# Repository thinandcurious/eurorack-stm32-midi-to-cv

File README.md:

# MIDI to CV

## STLink Pins

- VDD (Do not connect)
- SWCLK
- GND
- SWDIO
- RST
- SWO

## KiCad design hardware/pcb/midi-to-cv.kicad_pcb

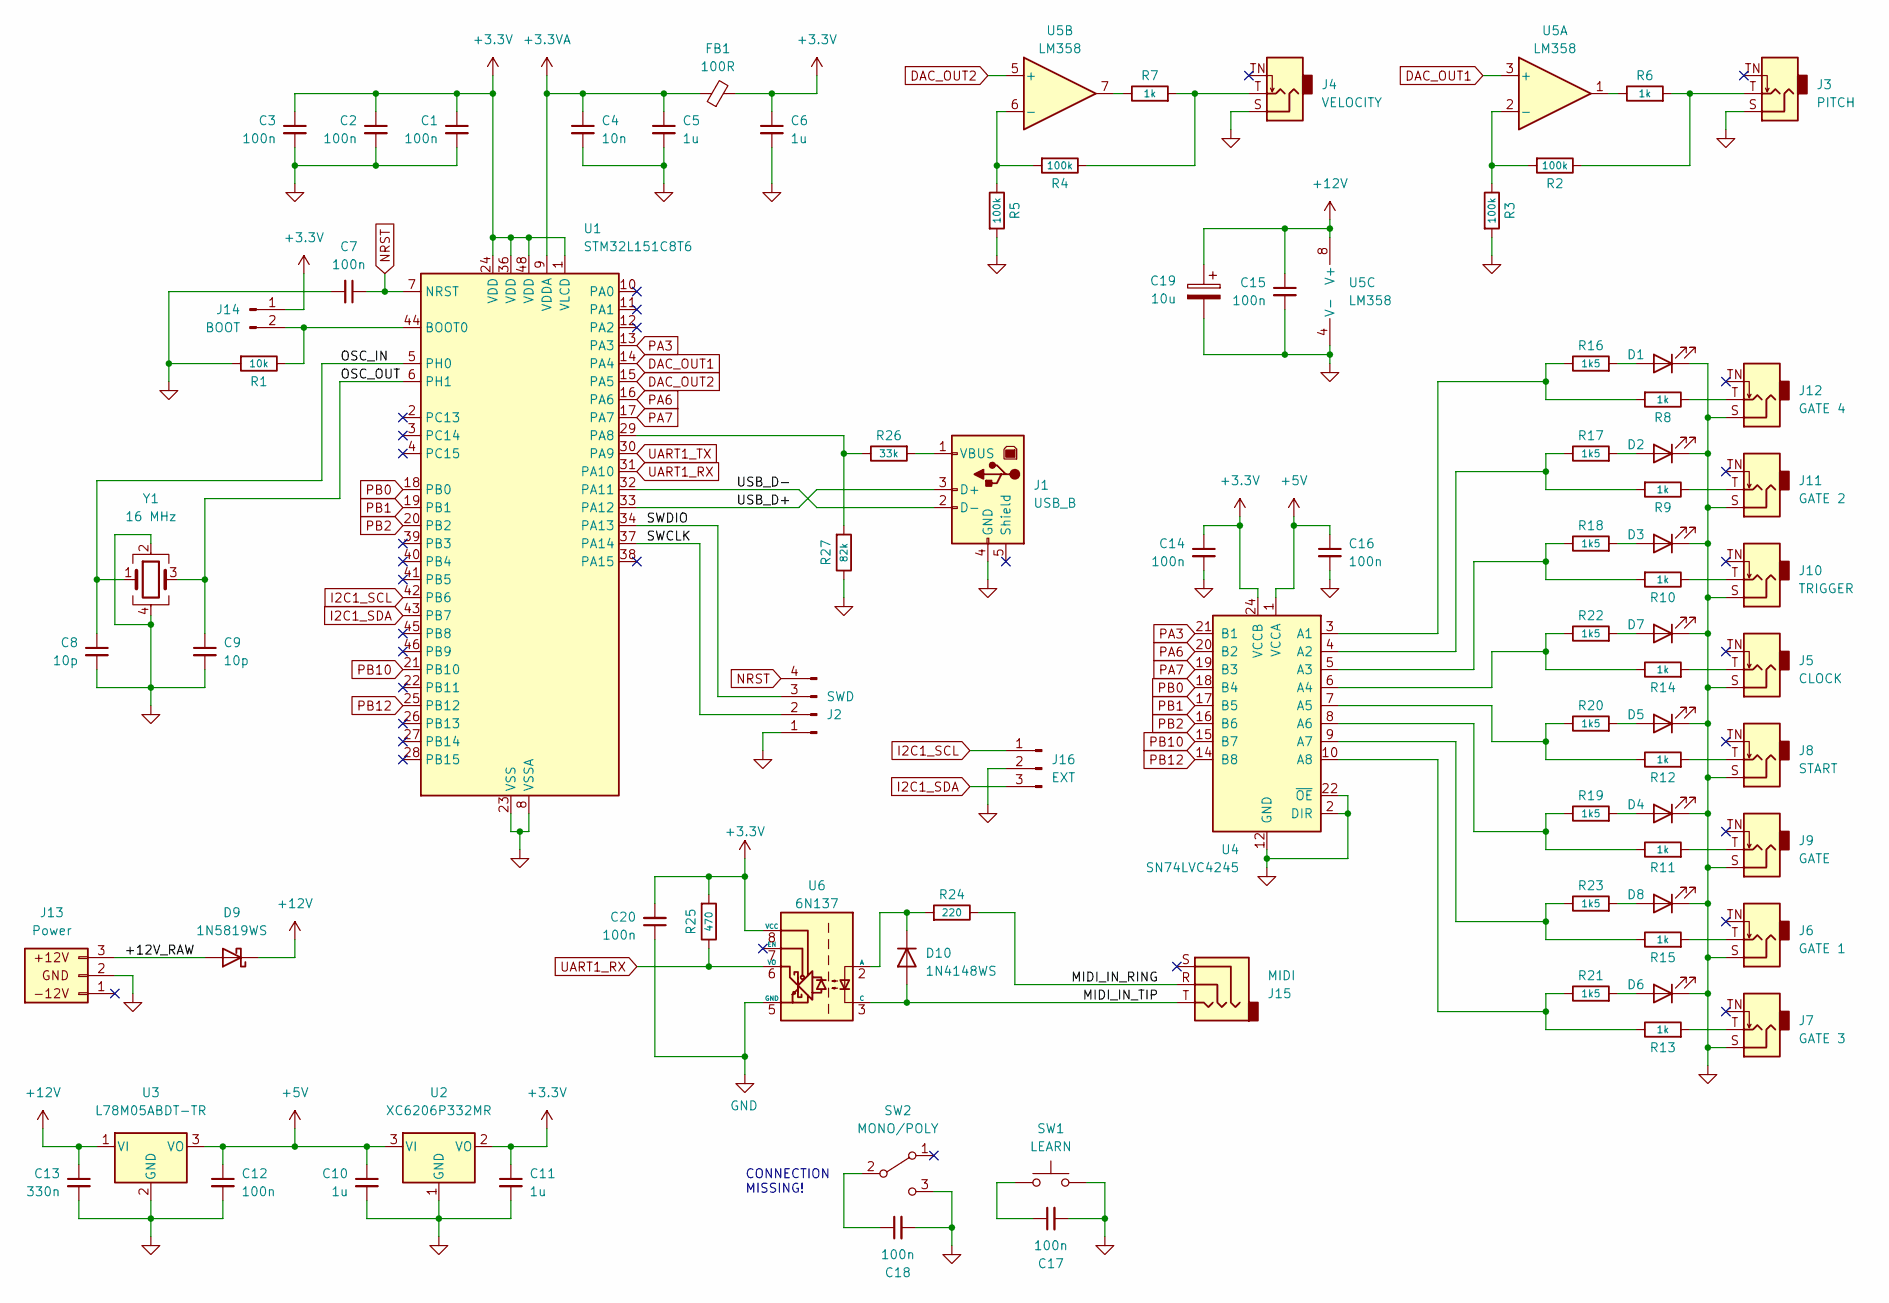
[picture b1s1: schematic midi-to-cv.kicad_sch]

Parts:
C1, C2, C3, C7, C14, C15, C16, C17, C18: 100n; C_0402_1005Metric; LCSC C307331
C4: 10n; C_0402_1005Metric; LCSC C15195
C5, C6, C10, C11: 1u; C_0805_2012Metric; LCSC C28323
C8, C9: 10p; C_0402_1005Metric; LCSC C32949
C12: 100n; C_0805_2012Metric; LCSC C49678
C13: 330n; C_0805_2012Metric; LCSC C1740
C19: 10u; C_1206_3216Metric; LCSC C13585
C20: 100n; C_0603_1608Metric; LCSC C14663
D1, D2, D3, D4, D5, D6, D7, D8: LED; LED_D3.0mm_Centered
D9: 1N5819WS; D_SOD-323; LCSC C191023
D10: 1N4148WS; D_SOD-323; LCSC 1N4148WS
FB1: 100R; L_0805_2012Metric; LCSC C1002
J1: USB_B; Reichelt_FIS-USB-2-B-180
J2: SWD; PinHeader_1x04_P2.54mm_Vertical
J3: PITCH; Jack_3.5mm_PJ398SM_Vertical
J4: VELOCITY; Jack_3.5mm_PJ398SM_Vertical
J5: CLOCK; Jack_3.5mm_PJ398SM_Vertical
J6: GATE 1; Jack_3.5mm_PJ398SM_Vertical
J7: GATE 3; Jack_3.5mm_PJ398SM_Vertical
J8: START; Jack_3.5mm_PJ398SM_Vertical
J9: GATE; Jack_3.5mm_PJ398SM_Vertical
J10: TRIGGER; Jack_3.5mm_PJ398SM_Vertical
J11: GATE 2; Jack_3.5mm_PJ398SM_Vertical
J12: GATE 4; Jack_3.5mm_PJ398SM_Vertical
J13: Power; JST_XH_B3B-XH-A_1x03_P2.50mm_Vertical
J14: BOOT; PinHeader_1x02_P2.54mm_Vertical
J15: MIDI; Jack_3.5mm_PJ366ST_Vertical
J16: EXT; PinHeader_1x03_P2.54mm_Vertical
R1: 10k; R_0603_1608Metric; LCSC C25804
R2, R3, R4, R5: 100k; R_0603_1608Metric; LCSC C25803
R6, R7, R8, R9, R10, R11, R12, R13, R14, R15: 1k; R_0603_1608Metric; LCSC C21190
R16, R17, R18, R19, R20, R21, R22, R23: 1k5; R_0603_1608Metric; LCSC C22843
R24: 220; R_0603_1608Metric; LCSC C22962
R25: 470; R_0603_1608Metric; LCSC C23179
R26: 33k; R_0603_1608Metric; LCSC C4216
R27: 82k; R_0603_1608Metric; LCSC C23254
SW1: LEARN; Switch_Push_6mm
SW2: MONO/POLY; Switch_SPDT_Micro-Toggle
U1: STM32L151C8T6; LQFP-48_7x7mm_P0.5mm; LCSC C9861
U2: XC6206P332MR; SOT-23-3; LCSC C5446
U3: L78M05ABDT-TR; TO-252-2; LCSC C58069
U4: SN74LVC4245; TSSOP-24_4.4x7.8mm_P0.65mm; LCSC C7859
U5: LM358; SOIC-8_3.9x4.9mm_P1.27mm; LCSC C7950
U6: 6N137; SSO-8_6.7x9.8mm_P2.54mm_Clearance8mm; LCSC C110020
Y1: 16 MHz; Crystal_SMD_3225-4Pin_3.2x2.5mm; LCSC C13738

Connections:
+3.3V: C1.1, C2.1, C3.1, C6.1, C11.1, C14.1, C20.2, FB1.2, J14.1, R25.2, U1.1 (VLCD), U1.24 (VDD), U1.36 (VDD), U1.48 (VDD), U2.2 (VO), U4.23 (VCCB), U4.24 (VCCB), U6.8 (VCC)
+3.3VA: C4.1, C5.1, FB1.1, U1.9 (VDDA)
+5V: C10.1, C12.1, C16.1, U2.3 (VI), U3.3 (VO), U4.1 (VCCA)
+12V: C13.1, C15.1, C19.1, D9.1 (K), U3.1 (VI), U5.8 (V+)
/+12V_RAW: D9.2 (A), J13.3
/MIDI_IN_RING: J15.R, R24.1
/MIDI_IN_TIP: D10.2 (A), J15.T, U6.3 (C)
/OSC_IN: C8.1, U1.5 (PH0), Y1.1
/OSC_OUT: C9.1, U1.6 (PH1), Y1.3
/SWCLK: J2.2, U1.37 (PA14)
/SWDIO: J2.3, U1.34 (PA13)
/USB_D+: J1.3 (D+), U1.33 (PA12)
/USB_D-: J1.2 (D-), U1.32 (PA11)
DAC_OUT1: U1.14 (PA4), U5.3 (+)
DAC_OUT2: U1.15 (PA5), U5.5 (+)
GND: C1.2, C2.2, C3.2, C4.2, C5.2, C6.2, C7.2, C8.2, C9.2, C10.2, C11.2, C12.2, C13.2, C14.2, C15.2, C16.2, C17.2, C18.2, C19.2, C20.1, D1.1 (K), D2.1 (K), D3.1 (K), D4.1 (K), D5.1 (K), D6.1 (K), D7.1 (K), D8.1 (K), J1.4 (GND), J2.1, J3.S, J4.S, J5.S, J6.S, J7.S, J8.S, J9.S, J10.S, J11.S, J12.S, J13.2, J16.2, R1.2, R3.2, R5.2, R27.1, SW1.2, SW2.3 (C), U1.8 (VSSA), U1.23 (VSS), U1.35 (VSS), U1.47 (VSS), U2.1 (GND), U3.2 (GND), U4.2 (DIR), U4.11 (GND), U4.12 (GND), U4.13 (GND), U4.22 (~OE), U5.4 (V-), U6.5 (GND), Y1.2, Y1.4
I2C1_SCL: J16.1, U1.42 (PB6)
I2C1_SDA: J16.3, U1.43 (PB7)
NRST: C7.1, J2.4, U1.7 (NRST)
unnamed: C17.1, SW1.1
unnamed: D1.2 (A), R16.2
unnamed: D2.2 (A), R17.2
unnamed: D3.2 (A), R18.2
unnamed: D4.2 (A), R19.2
unnamed: D5.2 (A), R20.2
unnamed: D6.2 (A), R21.2
unnamed: D7.2 (A), R22.2
unnamed: D8.2 (A), R23.2
unnamed: D10.1 (K), R24.2, U6.2 (A)
unnamed: J1.1 (VBUS), R26.2
unnamed: J3.T, R2.1, R6.2
unnamed: J4.T, R4.1, R7.2
unnamed: J5.T, R14.2
unnamed: J6.T, R15.2
unnamed: J7.T, R13.2
unnamed: J8.T, R12.2
unnamed: J9.T, R11.2
unnamed: J10.T, R10.1
unnamed: J11.T, R9.1
unnamed: J12.T, R8.1
unnamed: J14.2, R1.1, U1.44 (BOOT0)
unnamed: R6.1, U5.1
unnamed: R7.1, U5.7
unnamed: C18.1, SW2.2 (B)
unnamed: R26.1, R27.2, U1.29 (PA8)
unnamed: R8.2, R16.1, U4.3 (A1)
unnamed: R9.2, R17.1, U4.4 (A2)
unnamed: R10.2, R18.1, U4.5 (A3)
unnamed: R14.1, R22.1, U4.6 (A4)
unnamed: R12.1, R20.1, U4.7 (A5)
unnamed: R11.1, R19.1, U4.8 (A6)
unnamed: R15.1, R23.1, U4.9 (A7)
unnamed: R13.1, R21.1, U4.10 (A8)
unnamed: R2.2, R3.1, U5.2 (-)
unnamed: R4.2, R5.1, U5.6 (-)
PA3: U1.13 (PA3), U4.21 (B1)
PA6: U1.16 (PA6), U4.20 (B2)
PA7: U1.17 (PA7), U4.19 (B3)
PB0: U1.18 (PB0), U4.18 (B4)
PB1: U1.19 (PB1), U4.17 (B5)
PB2: U1.20 (PB2), U4.16 (B6)
PB10: U1.21 (PB10), U4.15 (B7)
PB12: U1.25 (PB12), U4.14 (B8)
UART1_RX: R25.1, U1.31 (PA10), U6.6 (VO)
UART1_TX: U1.30 (PA9)

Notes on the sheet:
CONNECTION MISSING!

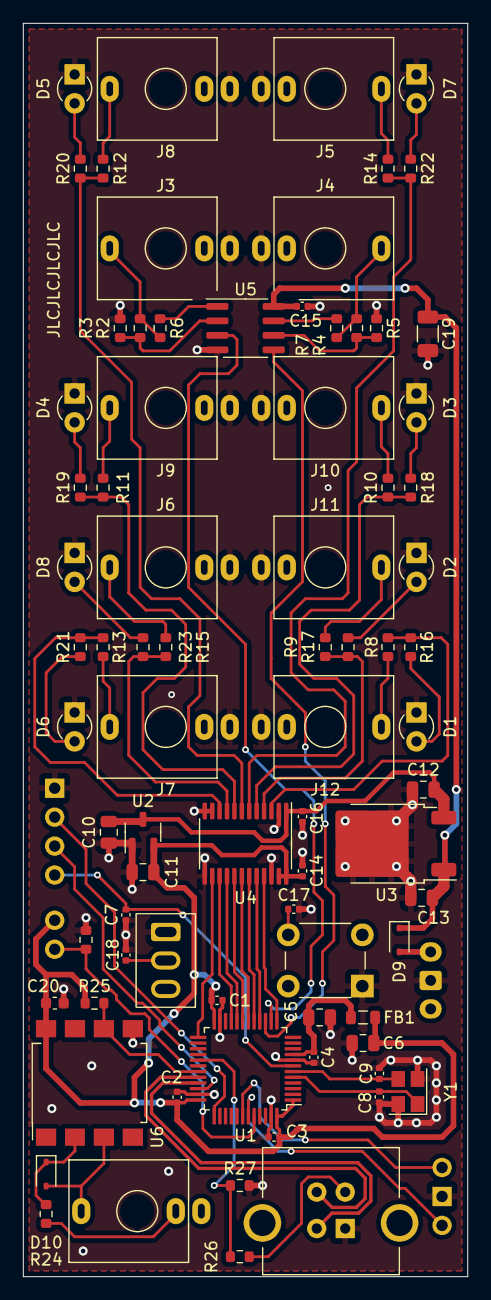
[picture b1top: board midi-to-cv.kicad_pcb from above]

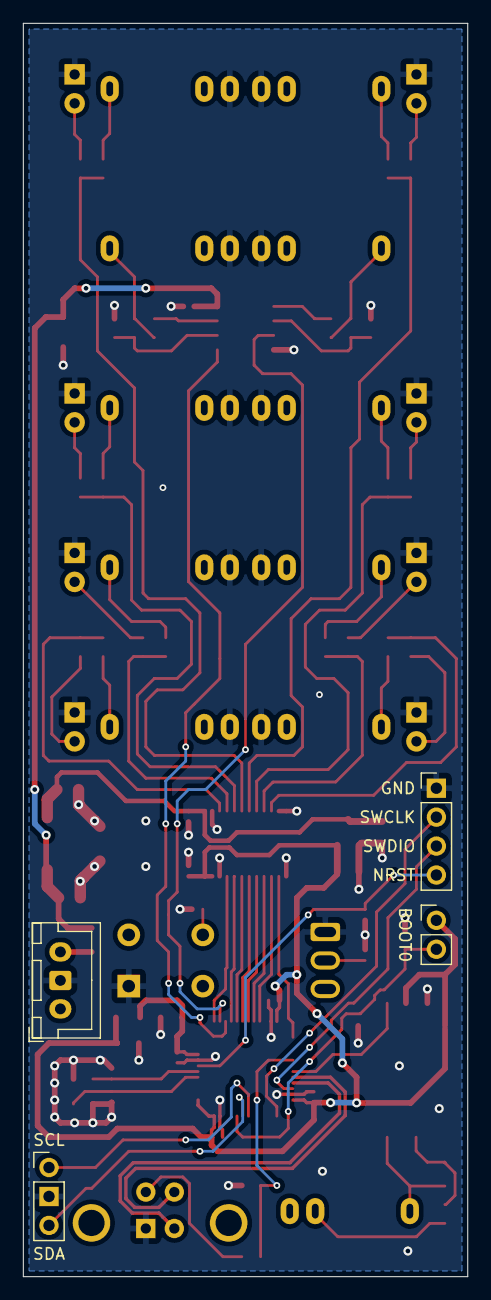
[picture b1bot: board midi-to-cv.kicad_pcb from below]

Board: 2 copper layers, 39.0 x 110.0 mm, 83 parts (4 on the bottom side), 64 nets.

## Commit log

2025-03-17 upload
